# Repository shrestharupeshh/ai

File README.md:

# ENSO Intelligence — Advanced El Niño / La Niña Tracker

A production-grade Next.js 15 climate intelligence dashboard for live ENSO monitoring, model forecasts, historical analogs, regional teleconnections, alerting, and a dedicated Nepal impact engine.

## Stack
- Next.js App Router + TypeScript + Tailwind CSS
- shadcn-style reusable components, Framer Motion, Recharts, Zustand, TanStack Query, Lucide icons
- API routes for ENSO status, forecasts, Nepal impacts, AI explanations, alerts, news, and CSV export
- PostgreSQL schema via Prisma, Redis-ready cache design, Docker and CI files

## Live data architecture
Collectors target NOAA CPC ERSSTv5/ONI text feeds first, with revalidated server fetches and deterministic scientific fallbacks when upstream climate endpoints are unavailable. The architecture is prepared for NOAA Climate.gov, IRI plume, ECMWF/Copernicus, BOM, NASA, DHM Nepal, ICIMOD, GPM IMERG, ERA5, and monsoon-index ingestion.

## Development
```bash
npm install
cp .env.example .env
npm run dev
```

## Quality checks
```bash
npm run typecheck
npm run test
npm run build
```

## API routes
- `GET /api/enso/status`
- `GET /api/enso/forecast`
- `GET /api/nepal/impact?region=kathmandu`
- `POST /api/ai/explain`
- `POST /api/alerts`
- `GET /api/news`
- `GET /api/export`

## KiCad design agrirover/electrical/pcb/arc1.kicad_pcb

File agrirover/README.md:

# AgriRover GH-1 — autonomous greenhouse inspection rover

A compact differential-drive rover that drives greenhouse aisles on its own, stops at fixed stations, photographs the
plants on both sides, logs air temperature, humidity, CO₂ and light, ties every observation to a plant position on a
map, and shows the results on a web dashboard. First crop: bench-grown lettuce. Inspection only — no spraying,
harvesting or manipulation.

| | |
|---|---|
| Size / mass | 482 × 354 × 1253 mm, 9.4 kg empty, 11.4 kg with 2 kg payload |
| Drive | 2 × Pololu 37D 70:1 gearmotors, 100 mm wheels, centre axle + 2 casters; 0.3 m/s in aisles, 0.5 m/s max; turns in place (Ø 0.56 m) |
| Power | 12.8 V 12 Ah LiFePO₄ with BMS; ≈ 16 W average → ≈ 7.8 h estimated |
| Compute | Raspberry Pi 5 (Ubuntu 24.04, ROS 2 Jazzy, Nav2) + STM32F411 real-time base controller |
| Sensing | RPLIDAR C1, wheel encoders, gyro, 2 RGB cameras with grey reference card, SHT45, SCD41, AS7341, contact bumper |
| Custom electronics | ARC-1 carrier board: fusing, reverse-polarity protection, E-stop chain with delayed cut, battery monitor |
| Prototype cost | ≈ 1 420 USD in parts (estimate, Nov 2026) |

## What exists, and how far each part has been taken

This repository is a design-and-software package produced **without hardware**. The table says exactly what has been
checked. Details and the physical test plan: [`docs/10_validation_test_report.md`](docs/10_validation_test_report.md).

| Deliverable | Where | State |
|---|---|---|
| Requirements, architecture, trade studies | `docs/01`–`03` | written; requirements cross-checked against the calculations by a test |
| Mechanical calculations | `mechanical/calcs/` | scripted, reproducible; analytical only |
| Parametric CAD: STEP assembly, part STEPs, STL, 3MF, DXF, dimensioned drawings | `mechanical/cad/`, `mechanical/export/` | generated with CadQuery; 0 interferences; purchased parts are envelope models; **not built** |
| Electrical calculations | `electrical/calcs/` | scripted; analytical only |
| ARC-1 schematic, 2-layer layout, Gerbers, drill, pick-and-place, BOM | `electrical/pcb/` | generated; KiCad-extracted netlist equals the design; KiCad DRC: 0 clearance/short/unconnected; **GUI ERC and human review still required; not fabricated** |
| Base-controller firmware | `firmware/` | portable core: 31 host checks pass; STM32 build links (6.6 kB); **never run on an MCU** |
| Core software: kinematics, planner, controller, localisation, vision, mission logic, storage | `software/agrirover/` | 39 automated tests pass, including 14 simulated system scenarios |
| Headless greenhouse simulator | `software/agrirover/sim/` | used for all scenario tests; simplified 2D model |
| Web dashboard + HTTP API | `dashboard/` | works against the simulator; API tests pass |
| ROS 2 Jazzy workspace: URDF, Nav2/AMCL/keep-out/EKF/SLAM configuration, Gazebo world, base bridge, mission and sensor nodes | `ros2_ws/` | statically checked only — **never executed** (ROS 2 could not be installed where this was written) |
| Computer vision | `software/agrirover/vision/`, `docs/07` | classical pipeline verified on **synthetic** images only; no trained model; no claim about real plants |
| BOM, sourcing, cost | `manufacturing/` | 33 lines; ~40 % of the cost on web-checked prices, the rest recalled/estimated and flagged |
| Assembly, operating, troubleshooting, safety documents | `docs/06`, `11`–`13` | written from the design; unproven until a build |
| Research extension | `research/` | three simulation model studies + proposal outline |

## Try it (no hardware, about five minutes)

```bash
cd agrirover
pip install -e "software[dashboard,dev]"

python -m agrirover.sim.run --out data/runtime/demo        # one full inspection mission in the reference greenhouse
python -m agrirover.sim.scenarios                          # 14 scenarios with pass/fail criteria (~1.5 min)
AGRIROVER_MODE=sim uvicorn dashboard.app:app --port 8080   # then open http://localhost:8080 and press "Start inspection"
```

## Rebuild every artefact from source

```bash
make calcs        # mechanical + electrical calculation reports
make cad          # STEP / STL / 3MF / DXF / drawings            (needs cadquery, matplotlib)
make pcb          # schematic, routed board, DRC, Gerbers, BOM   (needs KiCad 7, numpy, scipy, opencv)
make firmware     # host tests + STM32 cross-build               (needs gcc, arm-none-eabi-gcc)
make ros-assets   # map, keep-out mask, Gazebo world, stations from config/greenhouse.yaml
make test         # Python test-suite
make report       # docs/10_validation_test_report.md from the results above
make all
```

Single sources of truth: `config/rover.yaml` (robot), `config/greenhouse.yaml` (site),
`electrical/pcb/gen/design.py` (board netlist), `firmware/core/protocol.h` (wire protocol).

## Build order for a physical robot

1. Read `docs/13_safety.md` and the "not verified" table in `docs/10`.
2. Order purchased parts (`manufacturing/bom_master.csv`); measure them; correct CAD constants; cut plates, print parts.
3. Review ARC-1 in the KiCad GUI (ERC, footprints, Black Pill pinout), then order boards.
4. Assemble and bring up following `docs/06_assembly_guide.md`.
5. Install the software on the Pi (`ros2_ws/README.md`), survey the site (`docs/11` §9), calibrate the cameras (`docs/07` §5).
6. Execute the physical test plan (`docs/10` §4) before any unattended operation.

## Documentation

`docs/01_requirements` · `02_architecture` · `03_design_decisions` · `04_electrical` · `05_mechanical` ·
`06_assembly_guide` · `07_computer_vision` · `08_dashboard_api` · `09_manufacturing_guide` ·
`10_validation_test_report` · `11_operating_manual` · `12_troubleshooting` · `13_safety` · `research/README`

## Licence and dependencies

Project files: MIT (see `LICENSE`). Runtime dependencies are listed in `software/pyproject.toml` and
`ros2_ws/README.md`; all are open source (NumPy, SciPy, OpenCV, PyYAML, pyserial, FastAPI, uvicorn; optional ONNX
Runtime and Adafruit sensor drivers; ROS 2 Jazzy, Nav2, slam_toolbox, robot_localization, sllidar_ros2, v4l2_camera).
Design tools: CadQuery, KiCad 7, GCC.

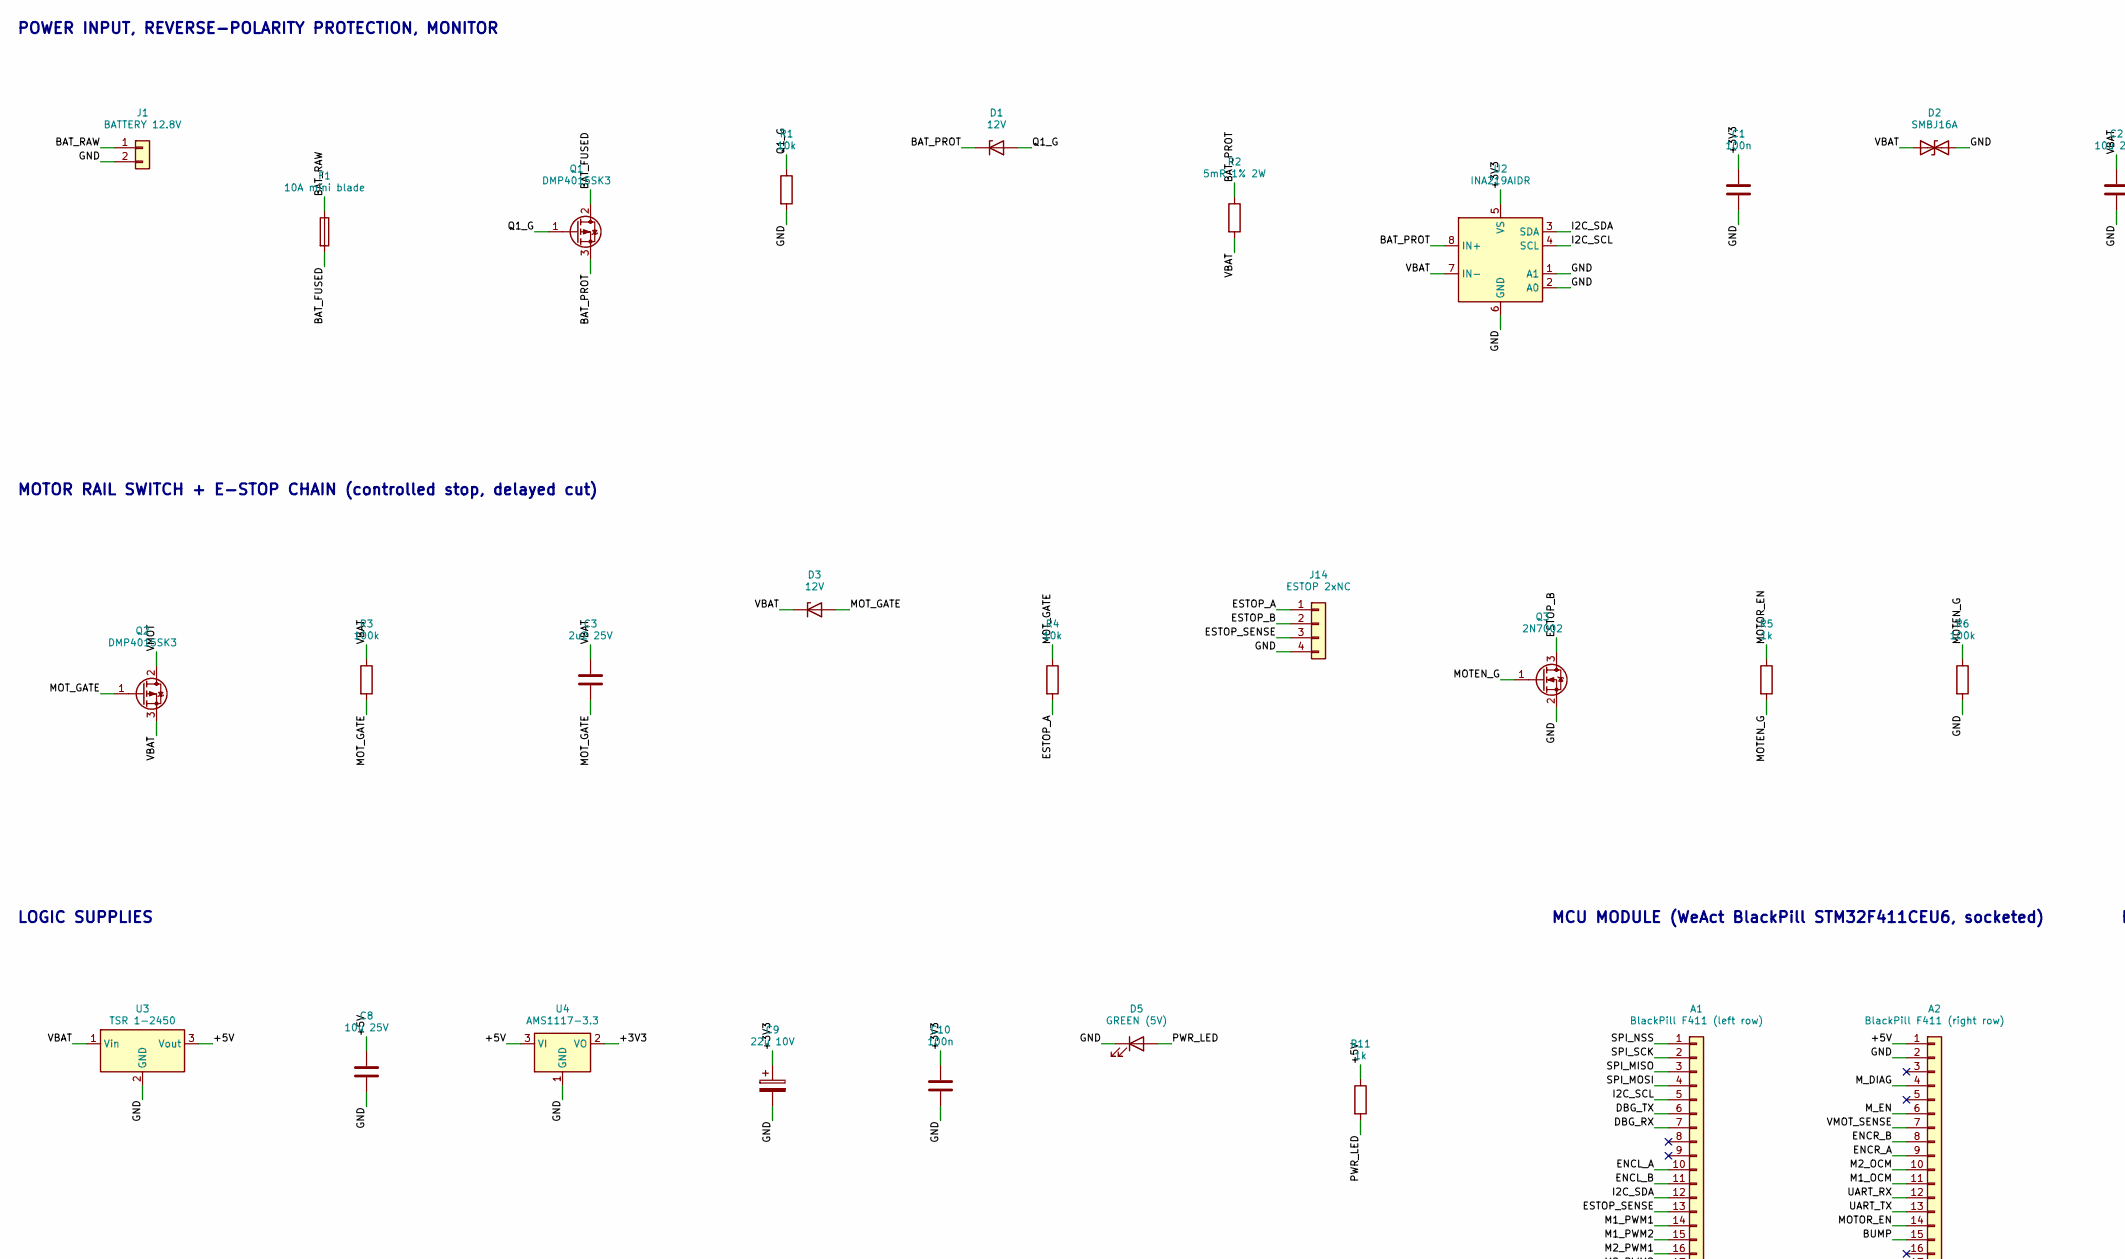
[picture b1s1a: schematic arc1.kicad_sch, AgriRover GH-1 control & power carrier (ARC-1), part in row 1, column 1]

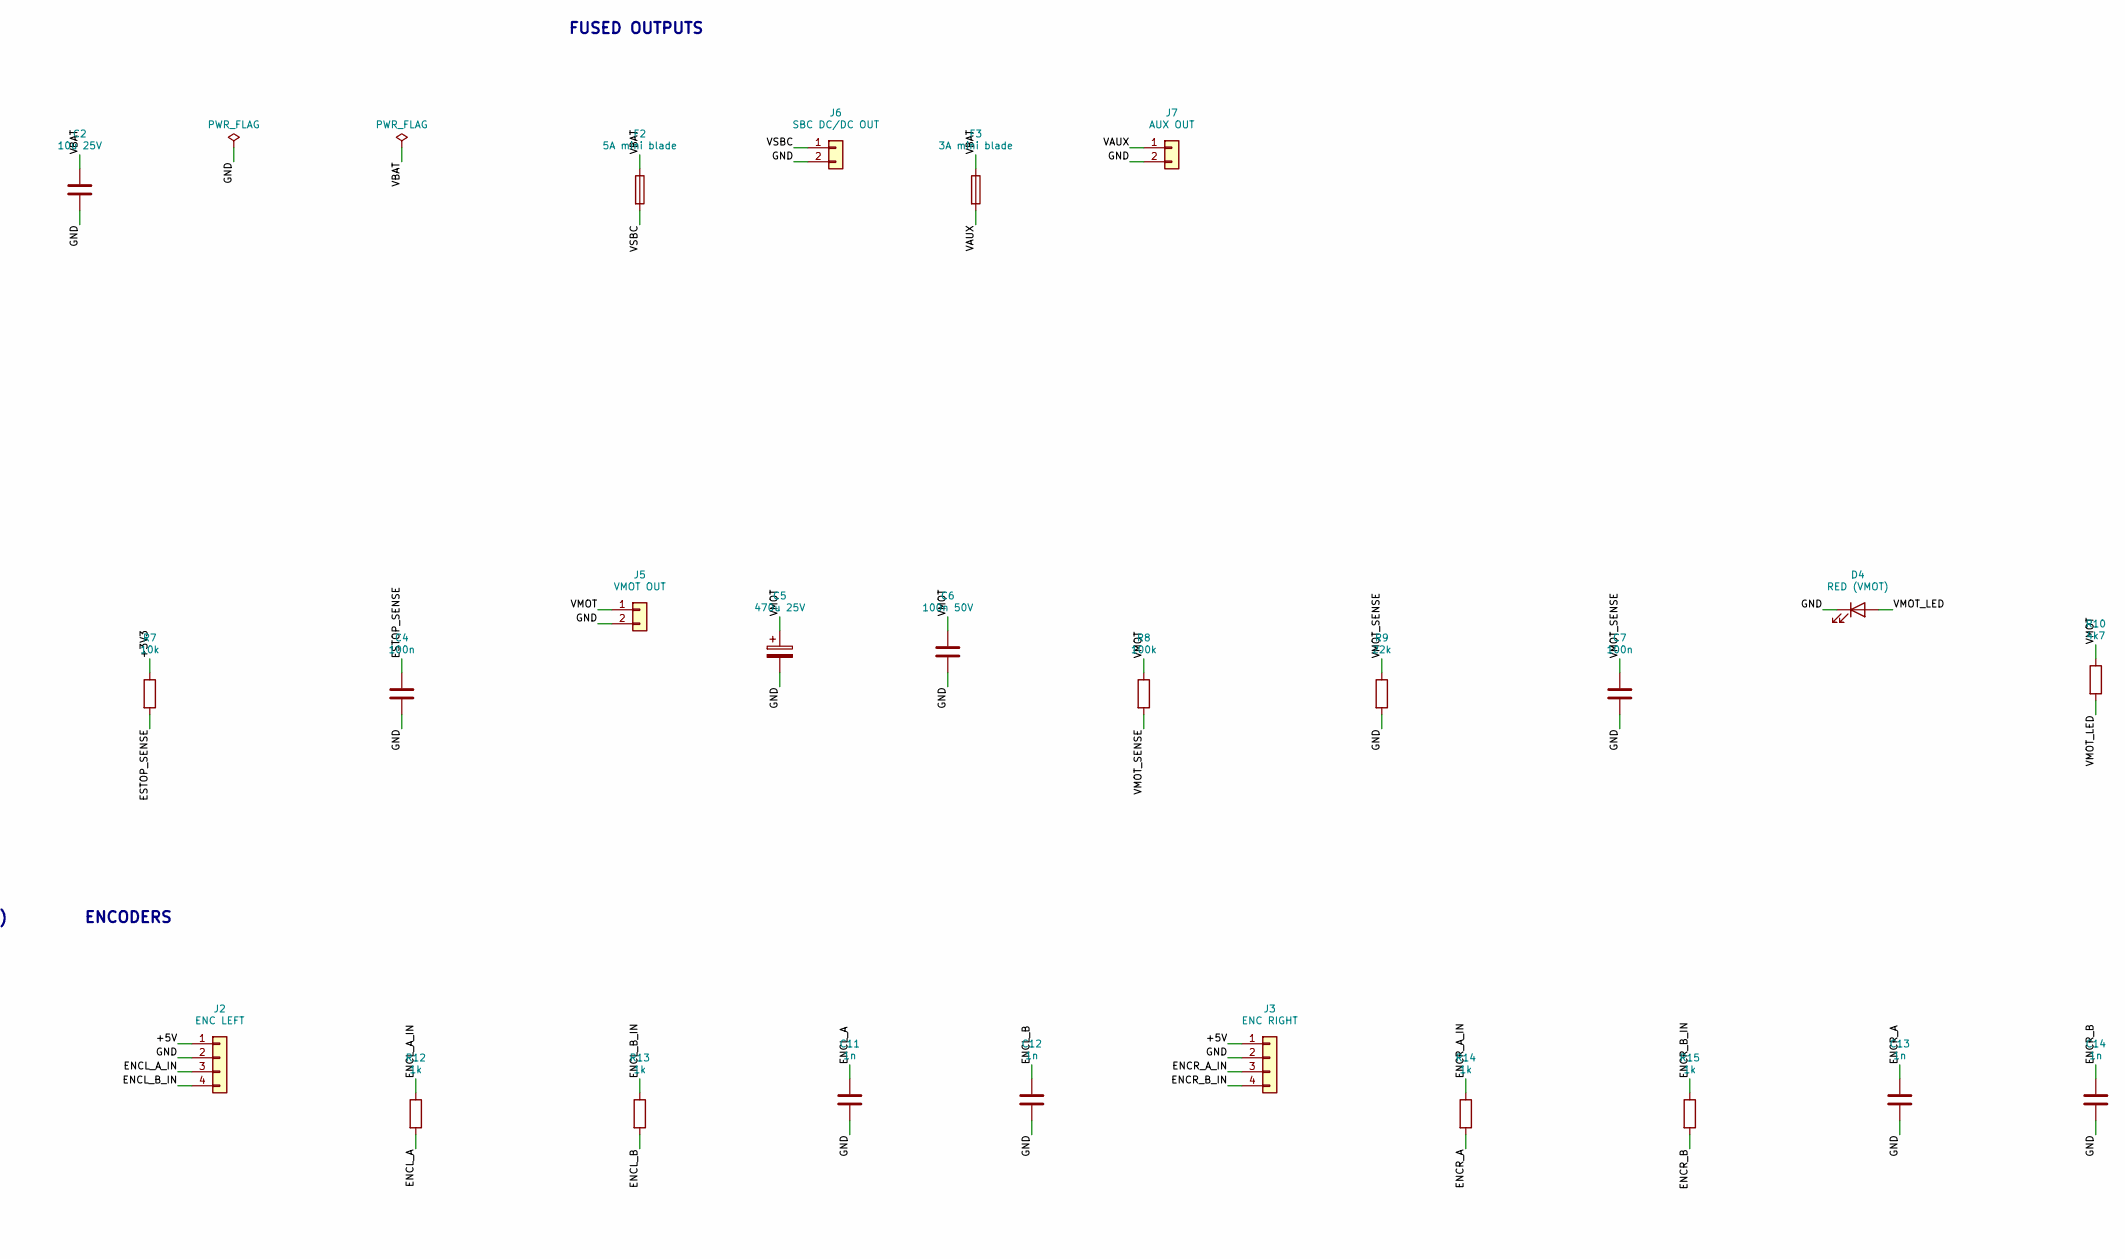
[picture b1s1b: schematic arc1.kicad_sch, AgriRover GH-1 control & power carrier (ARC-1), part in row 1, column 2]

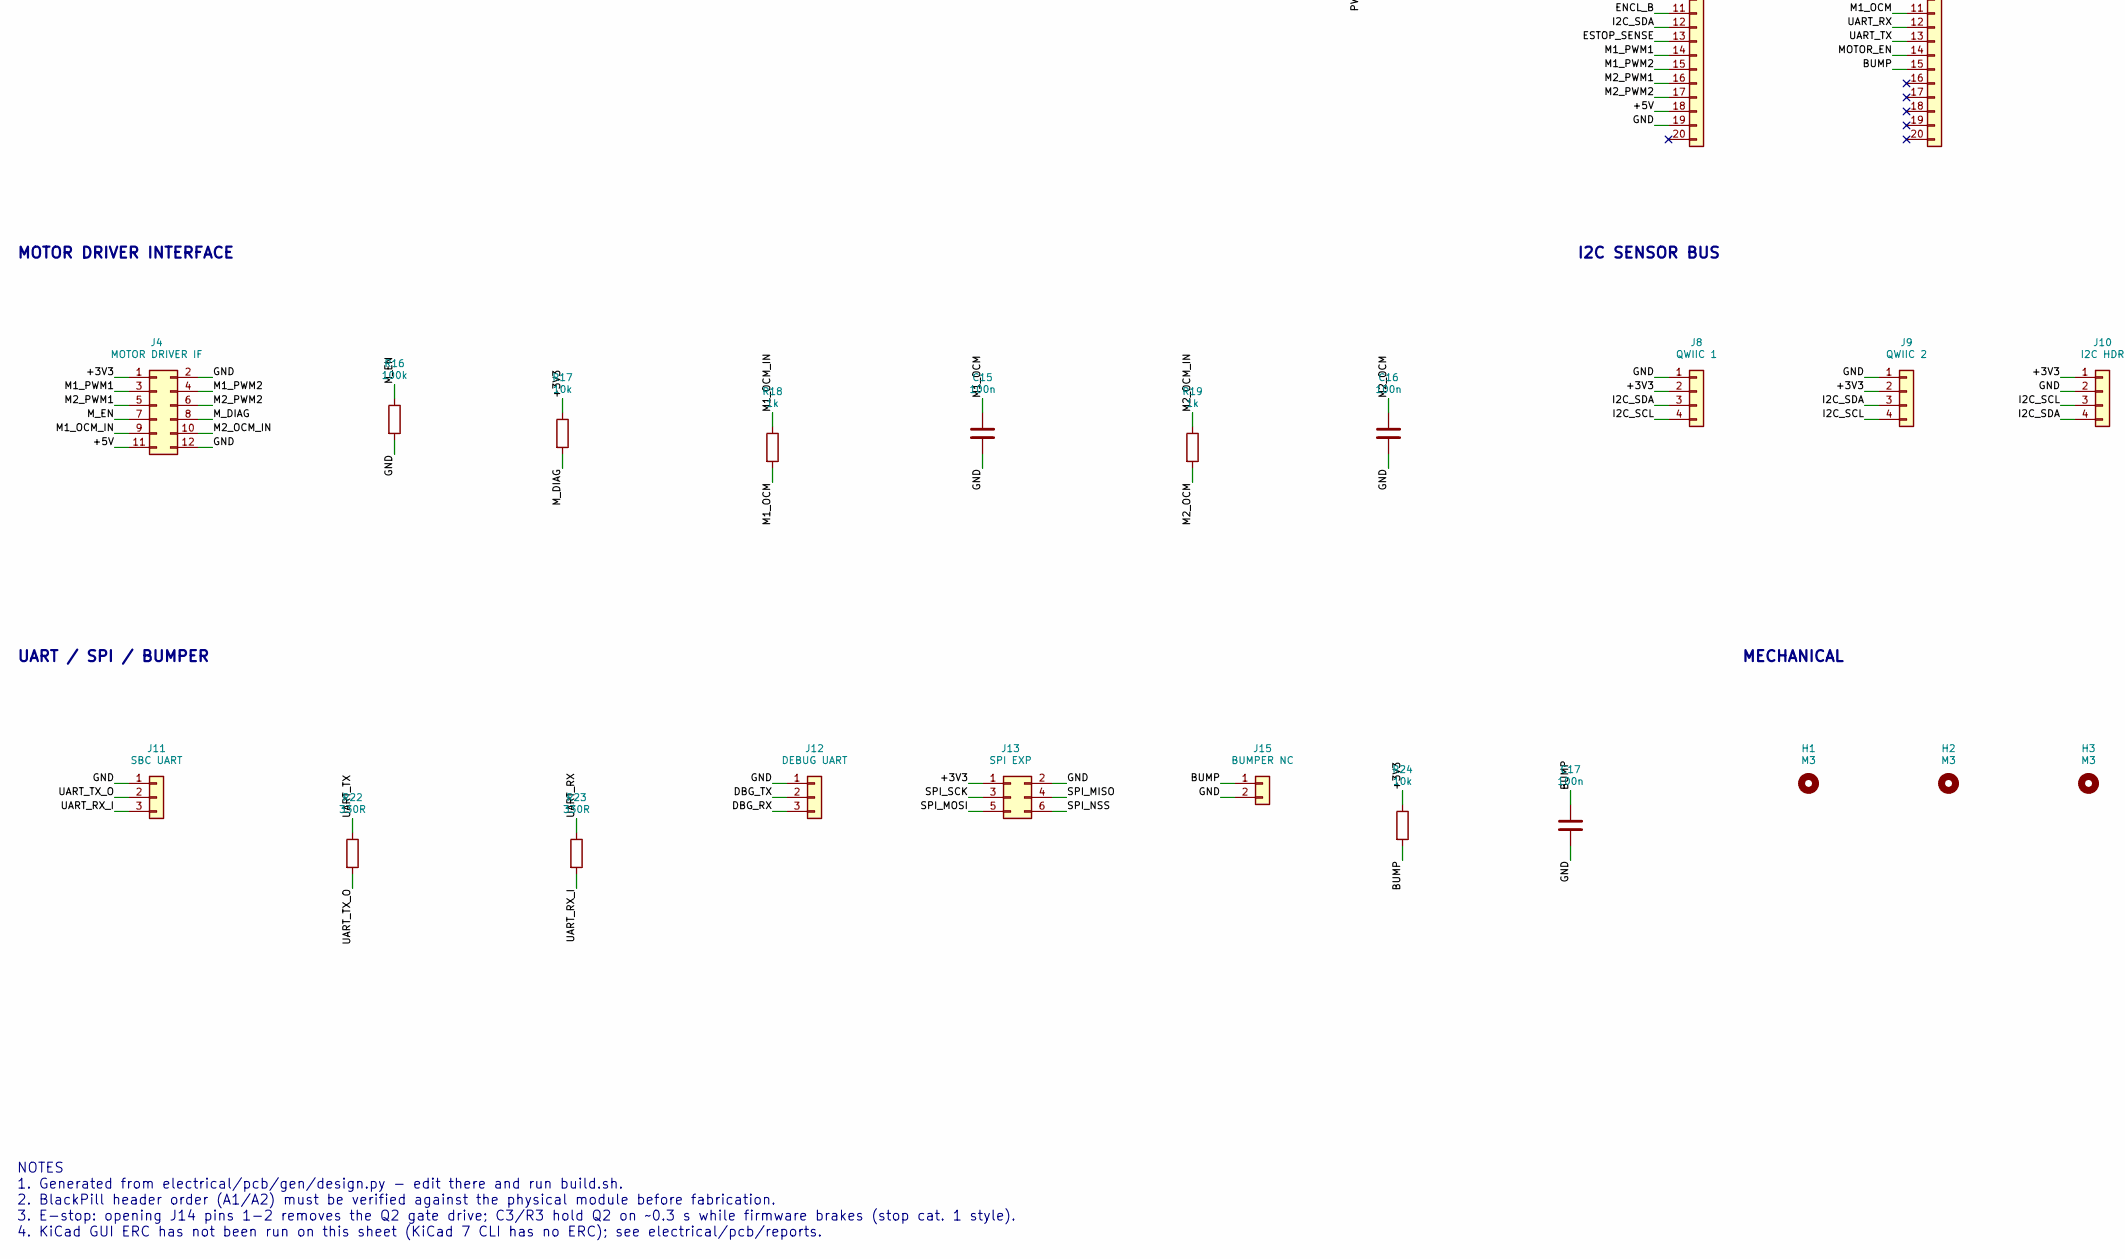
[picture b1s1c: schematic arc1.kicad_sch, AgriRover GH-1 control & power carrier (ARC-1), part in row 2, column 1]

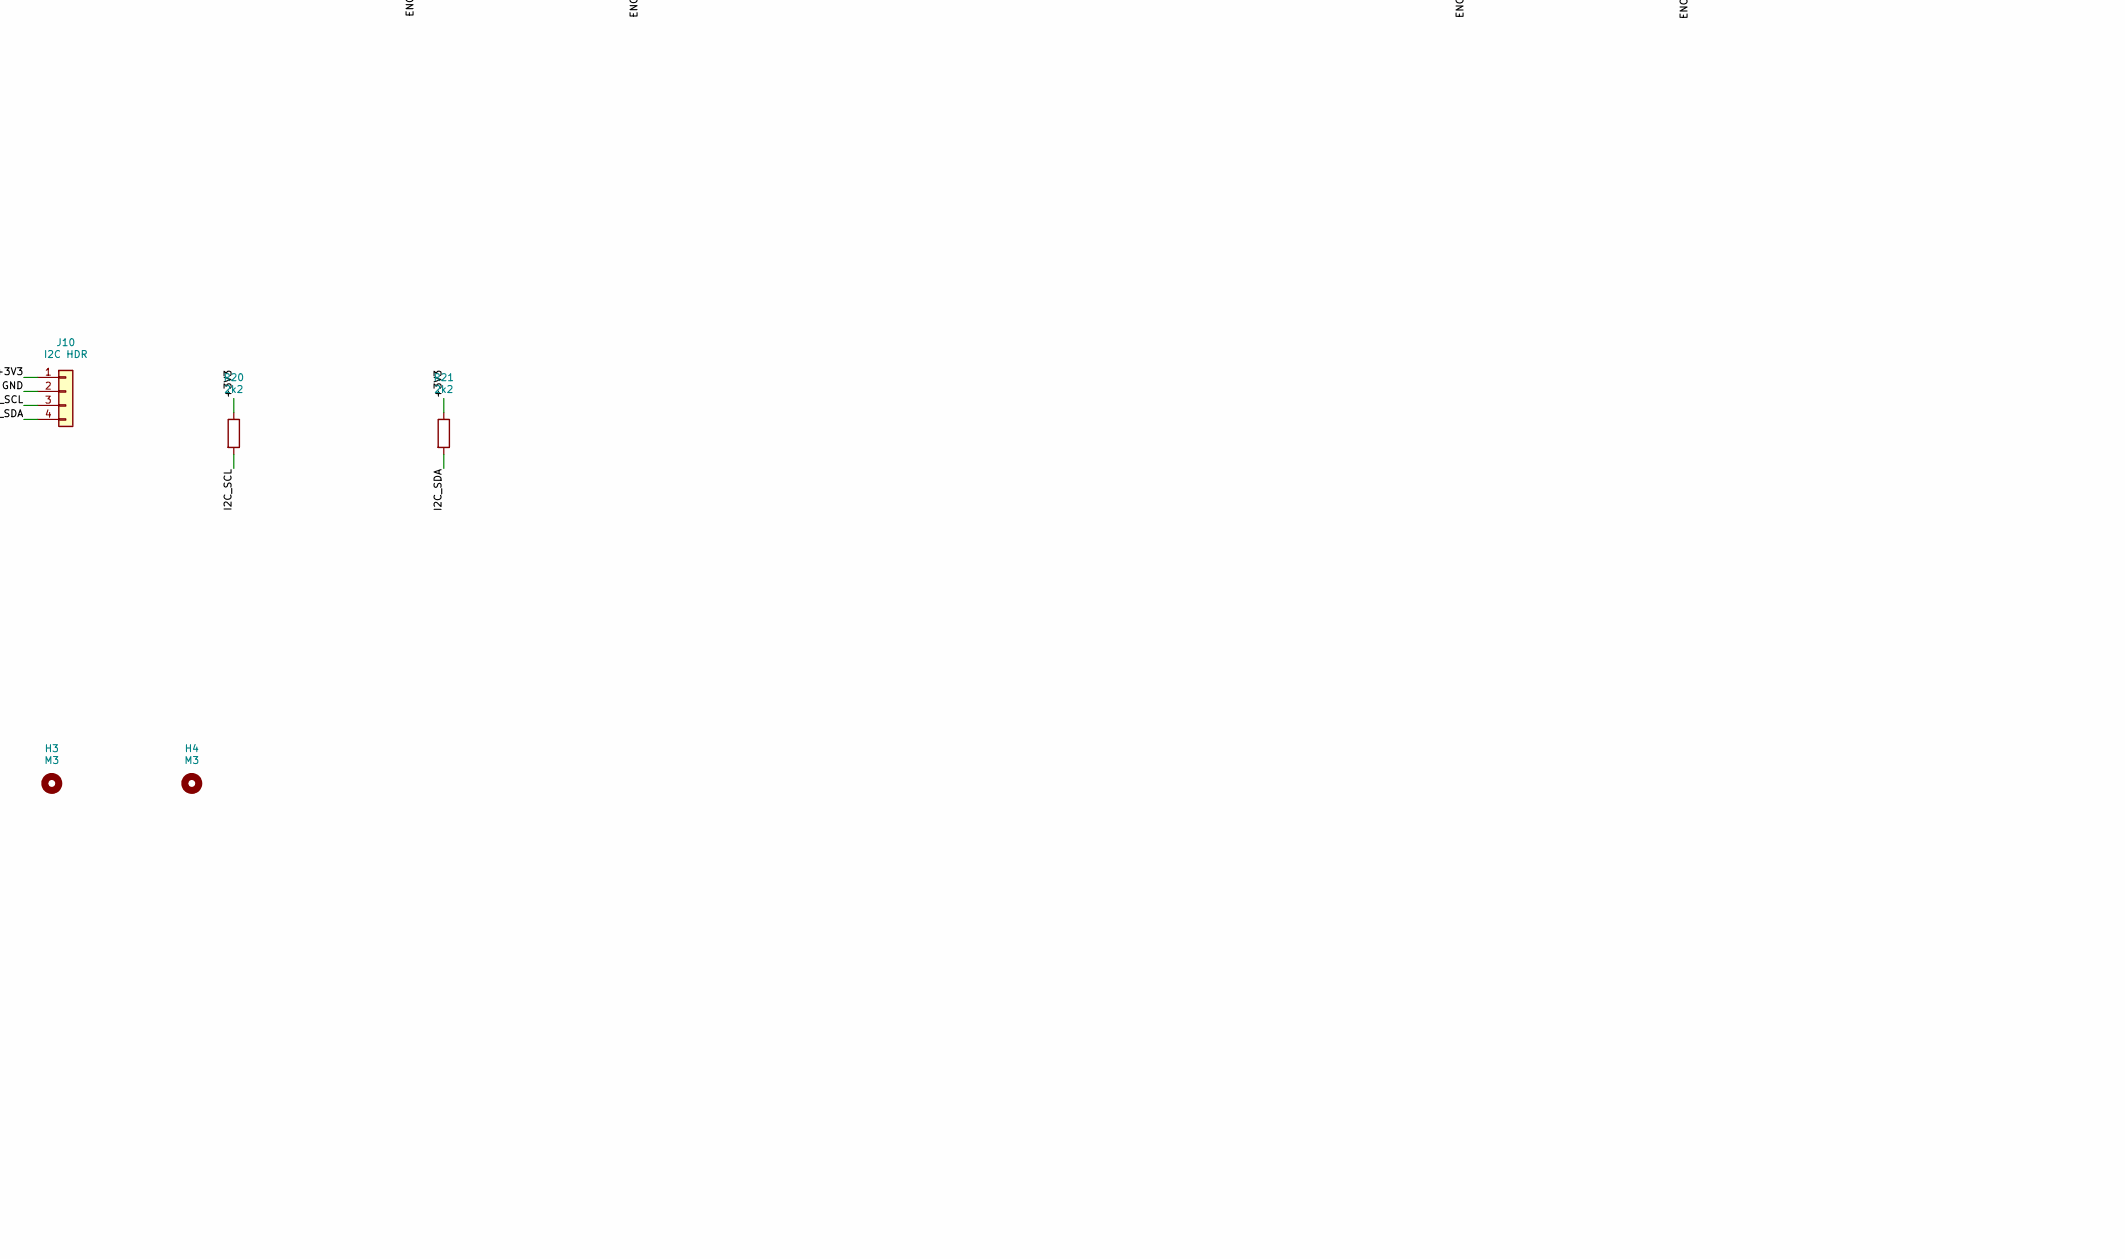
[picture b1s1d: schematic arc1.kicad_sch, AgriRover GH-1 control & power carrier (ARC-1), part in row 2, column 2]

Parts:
A1: BlackPill F411 (left row); PinSocket_1x20_P2.54mm_Vertical; MPN 4877
A2: BlackPill F411 (right row); PinSocket_1x20_P2.54mm_Vertical
C1, C4, C7, C10, C15, C16, C17: 100n; C_0805_2012Metric_Pad1.18x1.45mm_HandSolder
C2, C8: 10u 25V; C_1206_3216Metric_Pad1.33x1.80mm_HandSolder
C3: 2u2 25V; C_1206_3216Metric_Pad1.33x1.80mm_HandSolder
C5: 470u 25V; CP_Radial_D10.0mm_P5.00mm; MPN EEU-FR1E471
C6: 100n 50V; C_0805_2012Metric_Pad1.18x1.45mm_HandSolder
C9: 22u 10V; CP_EIA-3528-21_Kemet-B; MPN T491B226K010AT
C11, C12, C13, C14: 1n; C_0805_2012Metric_Pad1.18x1.45mm_HandSolder
D1, D3: 12V; D_SOD-123; MPN MMSZ5242B
D2: SMBJ16A; D_SMB; MPN SMBJ16A
D4: RED (VMOT); LED_0805_2012Metric_Pad1.15x1.40mm_HandSolder
D5: GREEN (5V); LED_0805_2012Metric_Pad1.15x1.40mm_HandSolder
F1: 10A mini blade; Fuseholder_Blade_Mini_Keystone_3568; MPN 3568
F2: 5A mini blade; Fuseholder_Blade_Mini_Keystone_3568; MPN 3568
F3: 3A mini blade; Fuseholder_Blade_Mini_Keystone_3568; MPN 3568
H1, H2, H3, H4: M3; MountingHole_3.2mm_M3
J1: BATTERY 12.8V; PhoenixContact_MSTBA_2,5_2-G-5,08_1x02_P5.08mm_Horizontal; MPN 1757242
J2: ENC LEFT; JST_XH_B4B-XH-A_1x04_P2.50mm_Vertical; MPN B4B-XH-A
J3: ENC RIGHT; JST_XH_B4B-XH-A_1x04_P2.50mm_Vertical; MPN B4B-XH-A
J4: MOTOR DRIVER IF; PinHeader_2x06_P2.54mm_Vertical
J5: VMOT OUT; PhoenixContact_MSTBA_2,5_2-G-5,08_1x02_P5.08mm_Horizontal; MPN 1757242
J6: SBC DC/DC OUT; PhoenixContact_MSTBA_2,5_2-G-5,08_1x02_P5.08mm_Horizontal; MPN 1757242
J7: AUX OUT; PhoenixContact_MSTBA_2,5_2-G-5,08_1x02_P5.08mm_Horizontal; MPN 1757242
J8: QWIIC 1; JST_SH_SM04B-SRSS-TB_1x04-1MP_P1.00mm_Horizontal; MPN SM04B-SRSS-TB
J9: QWIIC 2; JST_SH_SM04B-SRSS-TB_1x04-1MP_P1.00mm_Horizontal; MPN SM04B-SRSS-TB
J10: I2C HDR; PinHeader_1x04_P2.54mm_Vertical
J11: SBC UART; JST_XH_B3B-XH-A_1x03_P2.50mm_Vertical; MPN B3B-XH-A
J12: DEBUG UART; PinHeader_1x03_P2.54mm_Vertical
J13: SPI EXP; PinHeader_2x03_P2.54mm_Vertical
J14: ESTOP 2xNC; JST_XH_B4B-XH-A_1x04_P2.50mm_Vertical; MPN B4B-XH-A
J15: BUMPER NC; JST_XH_B2B-XH-A_1x02_P2.50mm_Vertical; MPN B2B-XH-A
Q1, Q2: DMP4015SK3; TO-252-2; MPN DMP4015SK3-13
Q3: 2N7002; SOT-23; MPN 2N7002
R1, R4, R7, R17, R24: 10k; R_0805_2012Metric_Pad1.20x1.40mm_HandSolder
R2: 5mR 1% 2W; R_2512_6332Metric; MPN WSL25125L000FEA18
R3, R6, R8, R16: 100k; R_0805_2012Metric_Pad1.20x1.40mm_HandSolder
R5, R11, R12, R13, R14, R15, R18, R19: 1k; R_0805_2012Metric_Pad1.20x1.40mm_HandSolder
R9: 22k; R_0805_2012Metric_Pad1.20x1.40mm_HandSolder
R10: 4k7; R_0805_2012Metric_Pad1.20x1.40mm_HandSolder
R20, R21: 2k2; R_0805_2012Metric_Pad1.20x1.40mm_HandSolder
R22, R23: 330R; R_0805_2012Metric_Pad1.20x1.40mm_HandSolder
U2: INA219AIDR; SOIC-8_3.9x4.9mm_P1.27mm; MPN INA219AIDR
U3: TSR 1-2450; Converter_DCDC_TRACO_TSR-1_THT; MPN TSR 1-2450
U4: AMS1117-3.3; SOT-223-3_TabPin2; MPN AMS1117-3.3

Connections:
+3V3: C1.1, C9.1, C10.1, J4.1, J8.2, J9.2, J10.1, J13.1, R7.1, R17.1, R20.1, R21.1, R24.1, U2.5 (VS), U4.2 (VO)
+5V: A1.18, A2.1, C8.1, J2.1, J3.1, J4.11, R11.1, U3.3 (Vout), U4.3 (VI)
BAT_FUSED: F1.2, Q1.2 (D)
BAT_PROT: D1.1 (K), Q1.3 (S), R2.1, U2.8 (IN+)
BAT_RAW: F1.1, J1.1
BUMP: A2.15, C17.1, J15.1, R24.2
DBG_RX: A1.7, J12.3
DBG_TX: A1.6, J12.2
ENCL_A: A1.10, C11.1, R12.2
ENCL_A_IN: J2.3, R12.1
ENCL_B: A1.11, C12.1, R13.2
ENCL_B_IN: J2.4, R13.1
ENCR_A: A2.9, C13.1, R14.2
ENCR_A_IN: J3.3, R14.1
ENCR_B: A2.8, C14.1, R15.2
ENCR_B_IN: J3.4, R15.1
ESTOP_A: J14.1, R4.2
ESTOP_B: J14.2, Q3.3 (D)
ESTOP_SENSE: A1.13, C4.1, J14.3, R7.2
GND: A1.19, A2.2, C1.2, C2.2, C4.2, C5.2, C6.2, C7.2, C8.2, C9.2, C10.2, C11.2, C12.2, C13.2, C14.2, C15.2, C16.2, C17.2, D2.2 (A2), D4.1 (K), D5.1 (K), J1.2, J2.2, J3.2, J4.2, J4.12, J5.2, J6.2, J7.2, J8.1, J8.MP, J9.1, J9.MP, J10.2, J11.1, J12.1, J13.2, J14.4, J15.2, Q3.2 (S), R1.2, R6.2, R9.2, R16.2, U2.1 (A1), U2.2 (A0), U2.6 (GND), U3.2 (GND), U4.1 (GND)
I2C_SCL: A1.5, J8.4, J9.4, J10.3, R20.2, U2.4 (SCL)
I2C_SDA: A1.12, J8.3, J9.3, J10.4, R21.2, U2.3 (SDA)
M1_OCM: A2.11, C15.1, R18.2
M1_OCM_IN: J4.9, R18.1
M1_PWM1: A1.14, J4.3
M1_PWM2: A1.15, J4.4
M2_OCM: A2.10, C16.1, R19.2
M2_OCM_IN: J4.10, R19.1
M2_PWM1: A1.16, J4.5
M2_PWM2: A1.17, J4.6
MOTEN_G: Q3.1 (G), R5.2, R6.1
MOTOR_EN: A2.14, R5.1
MOT_GATE: C3.2, D3.2 (A), Q2.1 (G), R3.2, R4.1
M_DIAG: A2.4, J4.8, R17.2
M_EN: A2.6, J4.7, R16.1
PWR_LED: D5.2 (A), R11.2
Q1_G: D1.2 (A), Q1.1 (G), R1.1
SPI_MISO: A1.3, J13.4
SPI_MOSI: A1.4, J13.5
SPI_NSS: A1.1, J13.6
SPI_SCK: A1.2, J13.3
UART_RX: A2.12, R23.1
UART_RX_I: J11.3, R23.2
UART_TX: A2.13, R22.1
UART_TX_O: J11.2, R22.2
VAUX: F3.2, J7.1
VBAT: C2.1, C3.1, D2.1 (A1), D3.1 (K), F2.1, F3.1, Q2.3 (S), R2.2, R3.1, U2.7 (IN-), U3.1 (Vin)
VMOT: C5.1, C6.1, J5.1, Q2.2 (D), R8.1, R10.1
VMOT_LED: D4.2 (A), R10.2
VMOT_SENSE: A2.7, C7.1, R8.2, R9.1
VSBC: F2.2, J6.1

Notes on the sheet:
POWER INPUT, REVERSE-POLARITY PROTECTION, MONITOR
FUSED OUTPUTS
MOTOR RAIL SWITCH + E-STOP CHAIN (controlled stop, delayed cut)
LOGIC SUPPLIES
MCU MODULE (WeAct BlackPill STM32F411CEU6, socketed)
ENCODERS
MOTOR DRIVER INTERFACE
I2C SENSOR BUS
UART / SPI / BUMPER
MECHANICAL
NOTES 1. Generated from electrical/pcb/gen/design.py - edit there and run build.sh. 2. BlackPill header order (A1/A2) must be verified against the physical module before fabrication. 3. E-stop: opening J14 pins 1-2 removes the Q2 gate drive; C3/R3 hold Q2 on ~0.3 s while firmware brakes (stop cat. 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

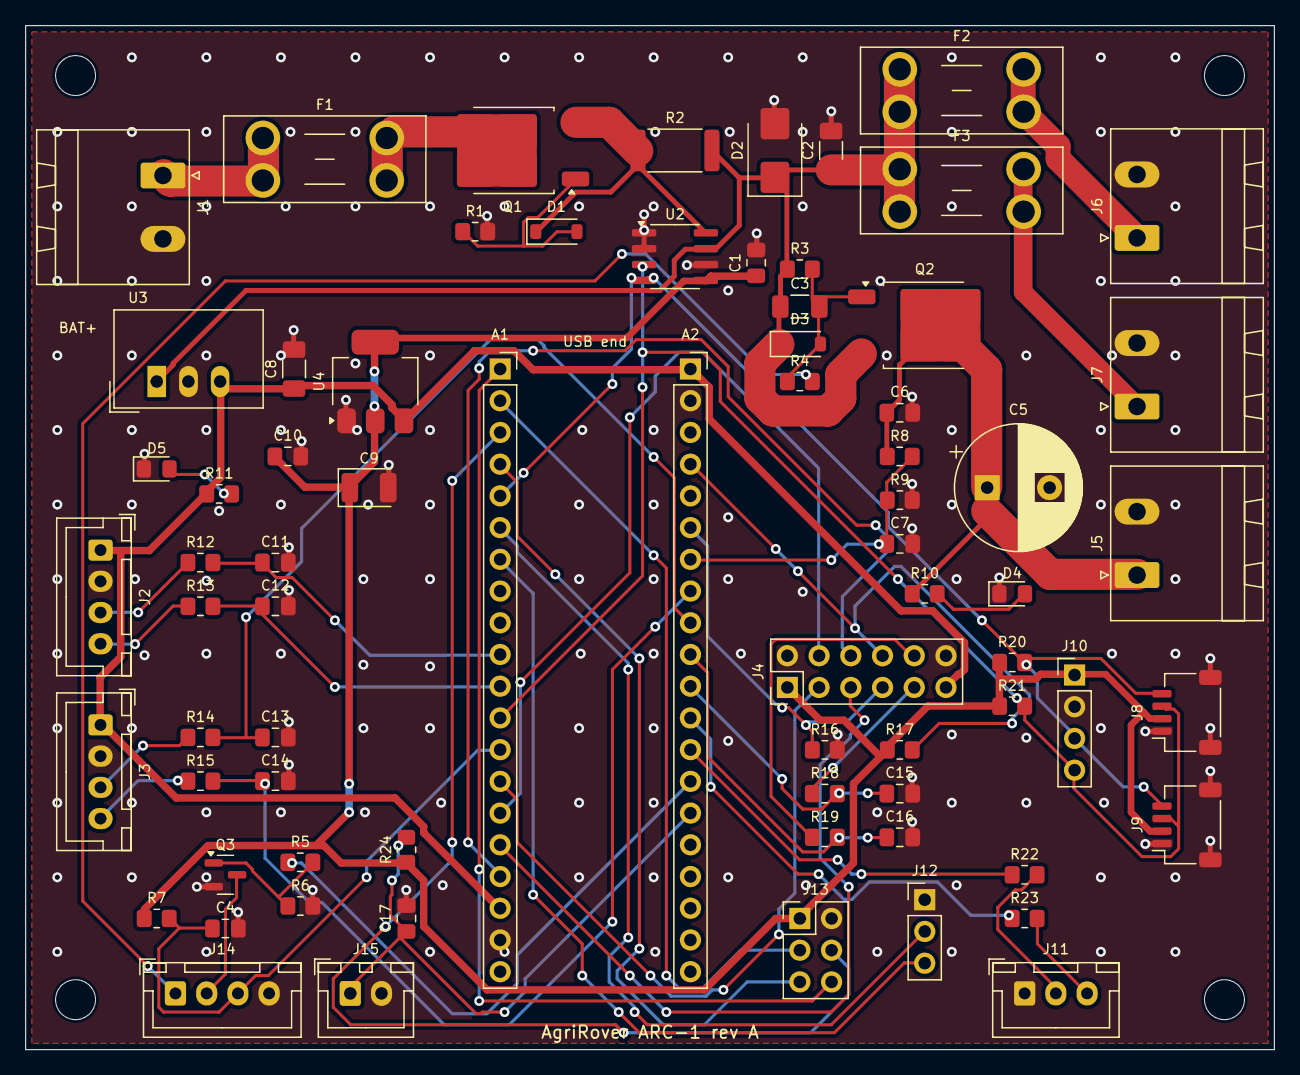
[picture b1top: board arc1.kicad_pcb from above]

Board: 2 copper layers, 100.0 x 82.0 mm, 76 parts (0 on the bottom side), 51 nets.

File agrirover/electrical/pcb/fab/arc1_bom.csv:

Item,Qty,References,Value,Footprint,Manufacturer,MPN,Description
1,1,A1,BlackPill F411 (left row),PinSocket_1x20_P2.54mm_Vertical,WeAct (via Adafruit),4877,"STM32F411CEU6 module, socketed"
2,7,C1 C4 C7 C10 C15 C16 C17,100n,C_0805_2012Metric_Pad1.18x1.45mm_HandSolder,any,,MLCC X7R
3,4,C11 C12 C13 C14,1n,C_0805_2012Metric_Pad1.18x1.45mm_HandSolder,any,,MLCC X7R
4,2,C2 C8,10u 25V,C_1206_3216Metric_Pad1.33x1.80mm_HandSolder,any,,MLCC X7R
5,1,C3,2u2 25V,C_1206_3216Metric_Pad1.33x1.80mm_HandSolder,any,,"MLCC X7R, sets ~0.3 s turn-off delay"
6,1,C5,470u 25V,CP_Radial_D10.0mm_P5.00mm,Panasonic,EEU-FR1E471,low-ESR electrolytic
7,1,C6,100n 50V,C_0805_2012Metric_Pad1.18x1.45mm_HandSolder,any,,MLCC X7R
8,1,C9,22u 10V,CP_EIA-3528-21_Kemet-B,KEMET,T491B226K010AT,"tantalum, LDO output"
9,2,D1 D3,12V,D_SOD-123,onsemi / Diodes,MMSZ5242B,zener 12 V gate clamp
10,1,D2,SMBJ16A,D_SMB,Littelfuse,SMBJ16A,"TVS 600 W, unidirectional (pad 1 = cathode)"
11,1,D4,RED (VMOT),LED_0805_2012Metric_Pad1.15x1.40mm_HandSolder,any,,LED 0805
12,1,D5,GREEN (5V),LED_0805_2012Metric_Pad1.15x1.40mm_HandSolder,any,,LED 0805
13,1,F1,10A mini blade,Fuseholder_Blade_Mini_Keystone_3568,Keystone,3568,mini blade fuse holder + 10 A fuse (Littelfuse 0297010)
14,1,F2,5A mini blade,Fuseholder_Blade_Mini_Keystone_3568,Keystone,3568,SBC buck feed fuse
15,1,F3,3A mini blade,Fuseholder_Blade_Mini_Keystone_3568,Keystone,3568,auxiliary feed fuse
16,1,J1,BATTERY 12.8V,"PhoenixContact_MSTBA_2,5_2-G-5,08_1x02_P5.08mm_Horizontal",Phoenix Contact,1757242,"MSTBA 2,5/2-G-5,08 header, 12 A"
17,1,J10,I2C HDR,PinHeader_1x04_P2.54mm_Vertical,any,,IMU breakout header
18,1,J11,SBC UART,JST_XH_B3B-XH-A_1x03_P2.50mm_Vertical,JST,B3B-XH-A,3.3 V UART to the SBC
19,1,J12,DEBUG UART,PinHeader_1x03_P2.54mm_Vertical,any,,
20,1,J13,SPI EXP,PinHeader_2x03_P2.54mm_Vertical,any,,expansion (e.g. MCP2515 CAN)
21,1,J14,ESTOP 2xNC,JST_XH_B4B-XH-A_1x04_P2.50mm_Vertical,JST,B4B-XH-A,"E-stop: pole 1 = pins 1-2, pole 2 = pins 3-4"
22,1,J15,BUMPER NC,JST_XH_B2B-XH-A_1x02_P2.50mm_Vertical,JST,B2B-XH-A,series NC bumper switches
23,1,J2,ENC LEFT,JST_XH_B4B-XH-A_1x04_P2.50mm_Vertical,JST,B4B-XH-A,
24,1,J3,ENC RIGHT,JST_XH_B4B-XH-A_1x04_P2.50mm_Vertical,JST,B4B-XH-A,
25,1,J4,MOTOR DRIVER IF,PinHeader_2x06_P2.54mm_Vertical,any,,2x6 pin header 2.54 mm
26,1,J5,VMOT OUT,"PhoenixContact_MSTBA_2,5_2-G-5,08_1x02_P5.08mm_Horizontal",Phoenix Contact,1757242,to motor-driver carriers
27,1,J6,SBC DC/DC OUT,"PhoenixContact_MSTBA_2,5_2-G-5,08_1x02_P5.08mm_Horizontal",Phoenix Contact,1757242,
28,1,J7,AUX OUT,"PhoenixContact_MSTBA_2,5_2-G-5,08_1x02_P5.08mm_Horizontal",Phoenix Contact,1757242,
29,1,J8,QWIIC 1,JST_SH_SM04B-SRSS-TB_1x04-1MP_P1.00mm_Horizontal,JST,SM04B-SRSS-TB,Qwiic / STEMMA QT
30,1,J9,QWIIC 2,JST_SH_SM04B-SRSS-TB_1x04-1MP_P1.00mm_Horizontal,JST,SM04B-SRSS-TB,Qwiic / STEMMA QT
31,1,Q1,DMP4015SK3,TO-252-2,Diodes Inc.,DMP4015SK3-13,"P-MOSFET -40 V, reverse-polarity protection"
32,1,Q2,DMP4015SK3,TO-252-2,Diodes Inc.,DMP4015SK3-13,P-MOSFET motor-rail high-side switch
33,1,Q3,2N7002,SOT-23,onsemi / Nexperia,2N7002,"N-MOSFET, MCU motor-rail enable"
34,5,R1 R4 R7 R17 R24,10k,R_0805_2012Metric_Pad1.20x1.40mm_HandSolder,Yageo / any,,resistor 0805 1 %
35,1,R10,4k7,R_0805_2012Metric_Pad1.20x1.40mm_HandSolder,Yageo / any,,resistor 0805 1 %
36,1,R2,5mR 1% 2W,R_2512_6332Metric,Vishay,WSL25125L000FEA18,current shunt 2512
37,2,R20 R21,2k2,R_0805_2012Metric_Pad1.20x1.40mm_HandSolder,Yageo / any,,resistor 0805 1 %
38,2,R22 R23,330R,R_0805_2012Metric_Pad1.20x1.40mm_HandSolder,Yageo / any,,resistor 0805 1 %
39,4,R3 R6 R8 R16,100k,R_0805_2012Metric_Pad1.20x1.40mm_HandSolder,Yageo / any,,resistor 0805 1 %
40,8,R5 R11 R12 R13 R14 R15 R18 R19,1k,R_0805_2012Metric_Pad1.20x1.40mm_HandSolder,Yageo / any,,resistor 0805 1 %
41,1,R9,22k,R_0805_2012Metric_Pad1.20x1.40mm_HandSolder,Yageo / any,,resistor 0805 1 %
42,1,U2,INA219AIDR,SOIC-8_3.9x4.9mm_P1.27mm,Texas Instruments,INA219AIDR,"bus voltage / current monitor, I2C 0x40"
43,1,U3,TSR 1-2450,Converter_DCDC_TRACO_TSR-1_THT,Traco Power,TSR 1-2450,"5 V 1 A switching regulator, SIP-3"
44,1,U4,AMS1117-3.3,SOT-223-3_TabPin2,"AMS / equivalent (LM1117, AZ1117)",AMS1117-3.3,3.3 V 1 A LDO

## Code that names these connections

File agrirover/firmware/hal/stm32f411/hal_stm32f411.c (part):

/* STM32F411CEU6 ("Black Pill") HAL for the AgriRover base controller. Bare metal, HSI 16 MHz.
 *
 * STATUS: cross-compiles and links; NOT yet run on hardware. Pin map = electrical/pcb/gen/design.py (MCU_NETS).
 *   PA0  BUMP (in)        PA1  MOTOR_EN (out)   PA2/PA3 USART2 TX/RX      PA4/PA5 M1/M2 current monitor (ADC1 IN4/IN5)
 *   PA6/PA7 TIM3 enc R    PA8  I2C3 SCL         PA15/PB3 TIM2 enc L       PB0  VMOT sense (ADC1 IN8)
 *   PB1  M_EN (out)       PB4  I2C3 SDA         PB5  ESTOP_SENSE (in)     PB6..PB9 TIM4 CH1..4 PWM (M1_PWM1, M1_PWM2, M2_PWM1, M2_PWM2)
 *   PB10 M_DIAG (in, active low)                PC13 on-board LED (active low)
 */
#include <math.h>
#include "../hal.h"
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
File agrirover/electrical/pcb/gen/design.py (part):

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    ("D3", "Device:D_Zener", "12V", FP["SOD"], {"1": "VBAT", "2": "MOT_GATE"}, "MMSZ5242B", "onsemi / Diodes", "zener 12 V gate clamp"),
    _r("R4", "10k", "MOT_GATE", "ESTOP_A"),
    ("J14", "Connector_Generic:Conn_01x04", "ESTOP 2xNC", FP["XH4"],
     {"1": "ESTOP_A", "2": "ESTOP_B", "3": "ESTOP_SENSE", "4": "GND"}, "B4B-XH-A", "JST", "E-stop: pole 1 = pins 1-2, pole 2 = pins 3-4"),
    ("Q3", "Transistor_FET:2N7002", "2N7002", FP["SOT23"], {"1": "MOTEN_G", "2": "GND", "3": "ESTOP_B"}, "2N7002", "onsemi / Nexperia", "N-MOSFET, MCU motor-rail enable"),
    _r("R5", "1k", "MOTOR_EN", "MOTEN_G"),
    _r("R6", "100k", "MOTEN_G", "GND"),
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    # ------------------------------------------------------------ motor driver interface (2 x TB9051FTG carriers)
    ("J4", "Connector_Generic:Conn_02x06_Odd_Even", "MOTOR DRIVER IF", FP["H2x6"],
     {"1": "+3V3", "2": "GND", "3": "M1_PWM1", "4": "M1_PWM2", "5": "M2_PWM1", "6": "M2_PWM2",
      "7": "M_EN", "8": "M_DIAG", "9": "M1_OCM_IN", "10": "M2_OCM_IN", "11": "+5V", "12": "GND"}, "", "any", "2x6 pin header 2.54 mm"),
    _r("R16", "100k", "M_EN", "GND"), _r("R17", "10k", "+3V3", "M_DIAG"),
    _r("R18", "1k", "M1_OCM_IN", "M1_OCM"), _c("C15", "100n", "M1_OCM", "GND"),
    _r("R19", "1k", "M2_OCM_IN", "M2_OCM"), _c("C16", "100n", "M2_OCM", "GND"),
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
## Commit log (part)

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2026-04-18 Add MP4 export of Claude_Design_Vertical_Animation
    Captured the HTML animation as a 30s H.264 MP4 (540x960, 30fps) using
    puppeteer headless Chrome and ffmpeg frame encoding.
    https://claude.ai/code/session_01XEq8JAGCVxAgSU9WXKH4xT
2026-04-28 Revise README title and content
    Updated the title and description of the README.
2026-05-15 Build ENSO Intelligence dashboard
